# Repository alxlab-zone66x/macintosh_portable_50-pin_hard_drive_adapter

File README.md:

# Macintosh Portable 50-pin Hard Drive Adapter v1.1

An adapter to allow you to use any standard 50-pin SCSI device as the Macintosh Portable hard drive. In particular it would work well for connecting directly to the back of a 50-pin SCSI hard drive.

Join us in #skunkworks on [Discord](https://discord.gg/GKcvtgU7P9) to help make retro solutions available to all.

## Bill of Materials

| Quantity | Product Number           | Datasheet                                                    |
| :------- | ------------------------ | ------------------------------------------------------------ |
| 1        | BHR-34-VUA               | https://app.adam-tech.com/products/download/data_sheet/203218/bhr-xx-vua-data-sheet.pdf |
| 1        | SFH11-PBPC-D17-ST-BK     | https://s3.amazonaws.com/catalogspreads-pdf/PAGE123%20.100%20SFH11%20SERIES%20FEMALE%20HDR%20ST%20RA.pdf |
| 1        | 171825-4                 | https://media.digikey.com/pdf/Data%20Sheets/Tyco%20Electonics%20AMP%20PDFs/Post%20Headers%20(Board%20Applied).pdf |
| 1        | 1N5818-T                 | https://www.diodes.com/assets/Datasheets/ds23001.pdf         |
| 1        | 34-pin ribbon cable 20cm | https://www.aliexpress.com/item/32985603139.html?spm=a2g0s.9042311.0.0.8a744c4dZvpend |
| 1        | power cable              | https://www.aliexpress.com/item/1005002510893961.html?spm=a2g0s.9042311.0.0.38264c4dVYgWFl |

## License

This work is licensed under a <a rel="license" href="http://creativecommons.org/licenses/by-nc-sa/4.0/">Creative Commons Attribution-NonCommercial-ShareAlike 4.0 International License</a>.

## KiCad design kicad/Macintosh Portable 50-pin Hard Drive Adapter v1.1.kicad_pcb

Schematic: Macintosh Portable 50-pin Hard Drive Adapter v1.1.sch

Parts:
D1: DIODE; D_DO-41_SOD81_P10.16mm_Horizontal
J1: SCSI_SE_Internal_Conn_02x25_Odd_Even_MountingPin; PinSocket_2x25_P2.54mm_Vertical
J2: Mac_Portable_SCSI_SE_Conn_02x17_Odd_Even_Mounting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; IDC-Header_2x17_P2.54mm_Vertical
J3: 171825-4; TE_171825-4

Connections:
+5V: D1.1 (K), D1.2 (A), J1.26, J2.23, J2.24, J2.33, J2.34, J3.1
/+12v: J2.25, J2.26, J2.31, J2.32, J3.4
/ACK: J1.38, J2.7
/ATN: J1.32, J2.8
/BSY: J1.36, J2.9
/CD: J1.46, J2.4
/DB0: J1.2, J2.14
/DB1: J1.4, J2.15
/DB2: J1.6, J2.17
/DB3: J1.8, J2.18
/DB4: J1.10, J2.19
/DB5: J1.12, J2.20
/DB6: J1.14, J2.21
/DB7: J1.16, J2.22
/DBP: J1.18, J2.13
/IO: J1.50, J2.5
/MSG: J1.42, J2.3
/REQ: J1.48, J2.1
/RST: J1.40, J2.10
/SEL: J1.44, J2.12
GND: J1.1, J1.3, J1.5, J1.7, J1.9, J1.11, J1.13, J1.15, J1.17, J1.19, J1.20, J1.21, J1.22, J1.23, J1.24, J1.27, J1.28, J1.29, J1.30, J1.31, J1.33, J1.34, J1.35, J1.37, J1.39, J1.41, J1.43, J1.45, J1.47, J1.49, J2.2, J2.6, J2.11, J2.16, J2.27, J2.28, J2.29, J2.30, J3.2, J3.3

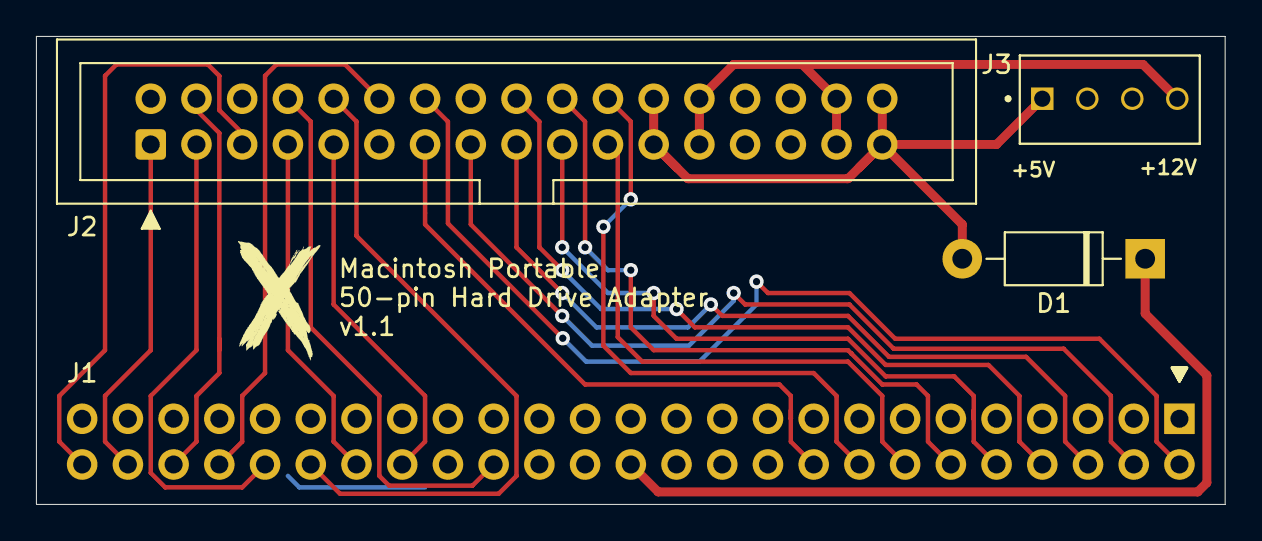
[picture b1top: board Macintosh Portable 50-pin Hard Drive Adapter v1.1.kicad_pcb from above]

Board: 2 copper layers, 66.0 x 26.0 mm, 4 parts (1 on the bottom side), 21 nets.

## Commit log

2021-06-20 Macintosh Portable 50-pin Hard Drive Adapter v1.0
2021-06-20 Add README image
2021-06-20 Add Creative Commons Attribution-NonCommercial-ShareAlike 4.0 International Public License
2021-06-24 Version 1.1
2021-06-24 FIx missing Discord image in README.md
